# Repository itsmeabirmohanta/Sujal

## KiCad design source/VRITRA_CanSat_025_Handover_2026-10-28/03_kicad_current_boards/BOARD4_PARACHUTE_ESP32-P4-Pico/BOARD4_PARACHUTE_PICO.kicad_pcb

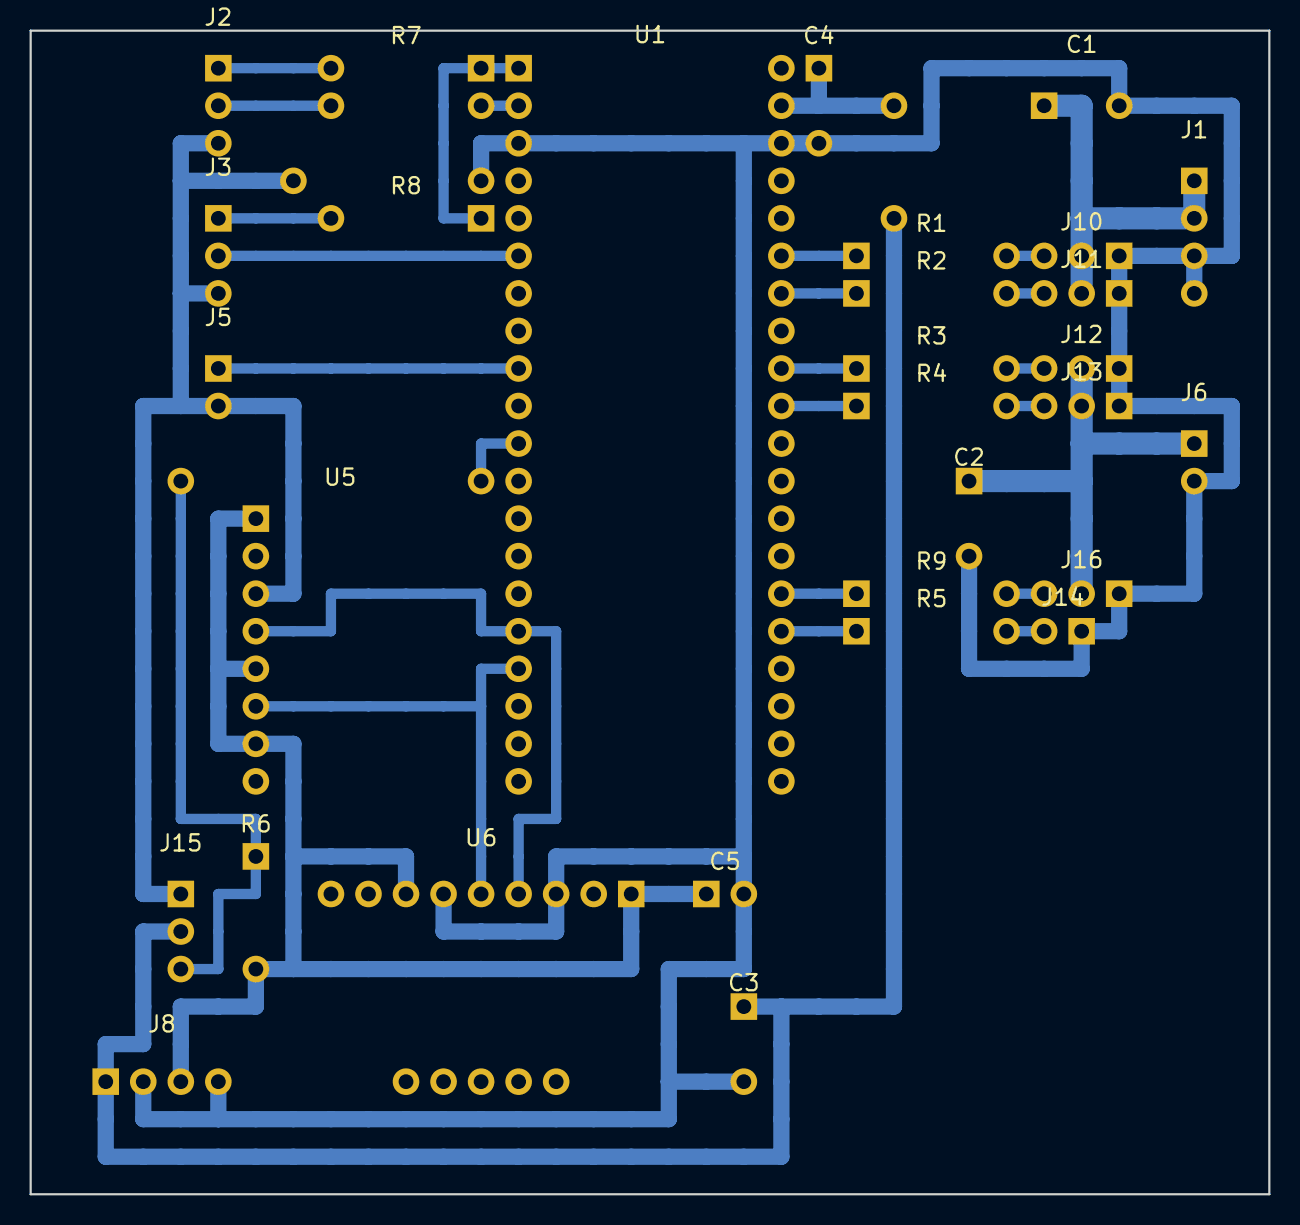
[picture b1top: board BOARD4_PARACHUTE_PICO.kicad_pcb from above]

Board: 2 copper layers, 83.8 x 78.7 mm, 34 parts (0 on the bottom side), 26 nets.

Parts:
C1: 470µF 8V rail
C2: 470µF 5VS rail
C3: 470µF logic
C4: 100nF at VSYS
C5: 100nF
J1: 8 V steer in (POWER J8)
J2: UART from MAIN J4
J3: UART to BACKUP J3
J5: GNSS from MAIN J8
J6: 5 V servo in (POWER J9)
J8: logic PWR (POWER J7)
J10: A20CLM LEFT steer (8 V)
J11: A20CLM RIGHT steer (8 V)
J12: MG90S #1 PARACHUTE BAY
J13: MG90S #2 PETRI PLATE
J14: ESC signal
J15: HALL sensor plug
J16: MG90S #3 EXTRA
LK1, LK2, LK3, LK4: wire link
R1, R2, R3, R4, R5, R9: 330
R6: 10k HALL↑3V3
R7: 1k TX2→A
R8: 1k TX→B
U1: ESP32-P4-Pico
U5: BMP585 (7Semi)
U6: LSM6DSO32 (Adafruit)

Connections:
+3V3_B: C5.1, J8.3 (+3V3), R6.2, U5.1 (VIN), U5.5 (SDO), U5.7 (CS), U6.1 (VIN), U6.7 (CS)
+5V_LOGIC: C3.1 (+), C4.1, J8.1 (+5V), J15.2 (+5V), LK1.1, U1.39 (VSYS)
+5V_SERVO: C2.1 (+), J6.1 (+5VS), J12.2 (+), J13.2 (+), J16.2 (+)
+8V_STEER: C1.1 (+), J1.1 (+8V), J1.2 (+8V), J10.2 (+), J11.2 (+)
BAY_LID: R3.1, U1.32 (GPIO22)
BAY_LID_S: J12.3 (S), R3.2
ESC: R5.1, U1.25 (GPIO33)
ESC_S: J14.2 (S), R5.2
GND: C1.2 (-), C2.2 (-), C3.2 (-), C4.2, C5.2, J1.3 (GND), J1.4 (GND), J2.3 (GND), J3.3 (GND), J5.2 (GND), J6.2 (GND), J8.2 (GND), J8.4 (GND), J10.1 (−), J11.1 (−), J12.1 (−), J13.1 (−), J14.1 (−), J15.1 (−), J16.1 (−), LK3.1, U1.3 (GND), U1.38 (GND), U5.3 (GND), U6.3 (GND), U6.6 (DO)
GNSS_IN: J5.1 (GNSS), U1.9 (GPIO14)
HALL: J15.3 (OUT), LK2.1, R6.1, U1.11 (GPIO5)
PETRI: R4.1, U1.31 (GPIO23)
PETRI_S: J13.3 (S), R4.2
RX2: J2.2 (RX2←A), LK4.1, U1.2 (GPIO19)
RX3: J3.2 (RX3←B), U1.6 (GPIO16)
SCL: U1.16 (GPIO8/SCL), U5.4 (SCK), U6.4 (SCL)
SDA: U1.17 (GPIO7/SDA), U5.6 (SDI), U6.5 (SDA)
SERVO_X: R9.1, U1.26 (GPIO32)
SERVO_X_S: J16.3 (S), R9.2
STEER_L: R1.1, U1.35 (GPIO20)
STEER_L_S: J10.3 (S), R1.2
STEER_R: R2.1, U1.34 (GPIO21)
STEER_R_S: J11.3 (S), R2.2
TX2: R7.1, R8.1, U1.1 (GPIO54)
TX2_A: J2.1 (TX2→A), R7.2
TX2_B: J3.1 (TX→B), R8.2

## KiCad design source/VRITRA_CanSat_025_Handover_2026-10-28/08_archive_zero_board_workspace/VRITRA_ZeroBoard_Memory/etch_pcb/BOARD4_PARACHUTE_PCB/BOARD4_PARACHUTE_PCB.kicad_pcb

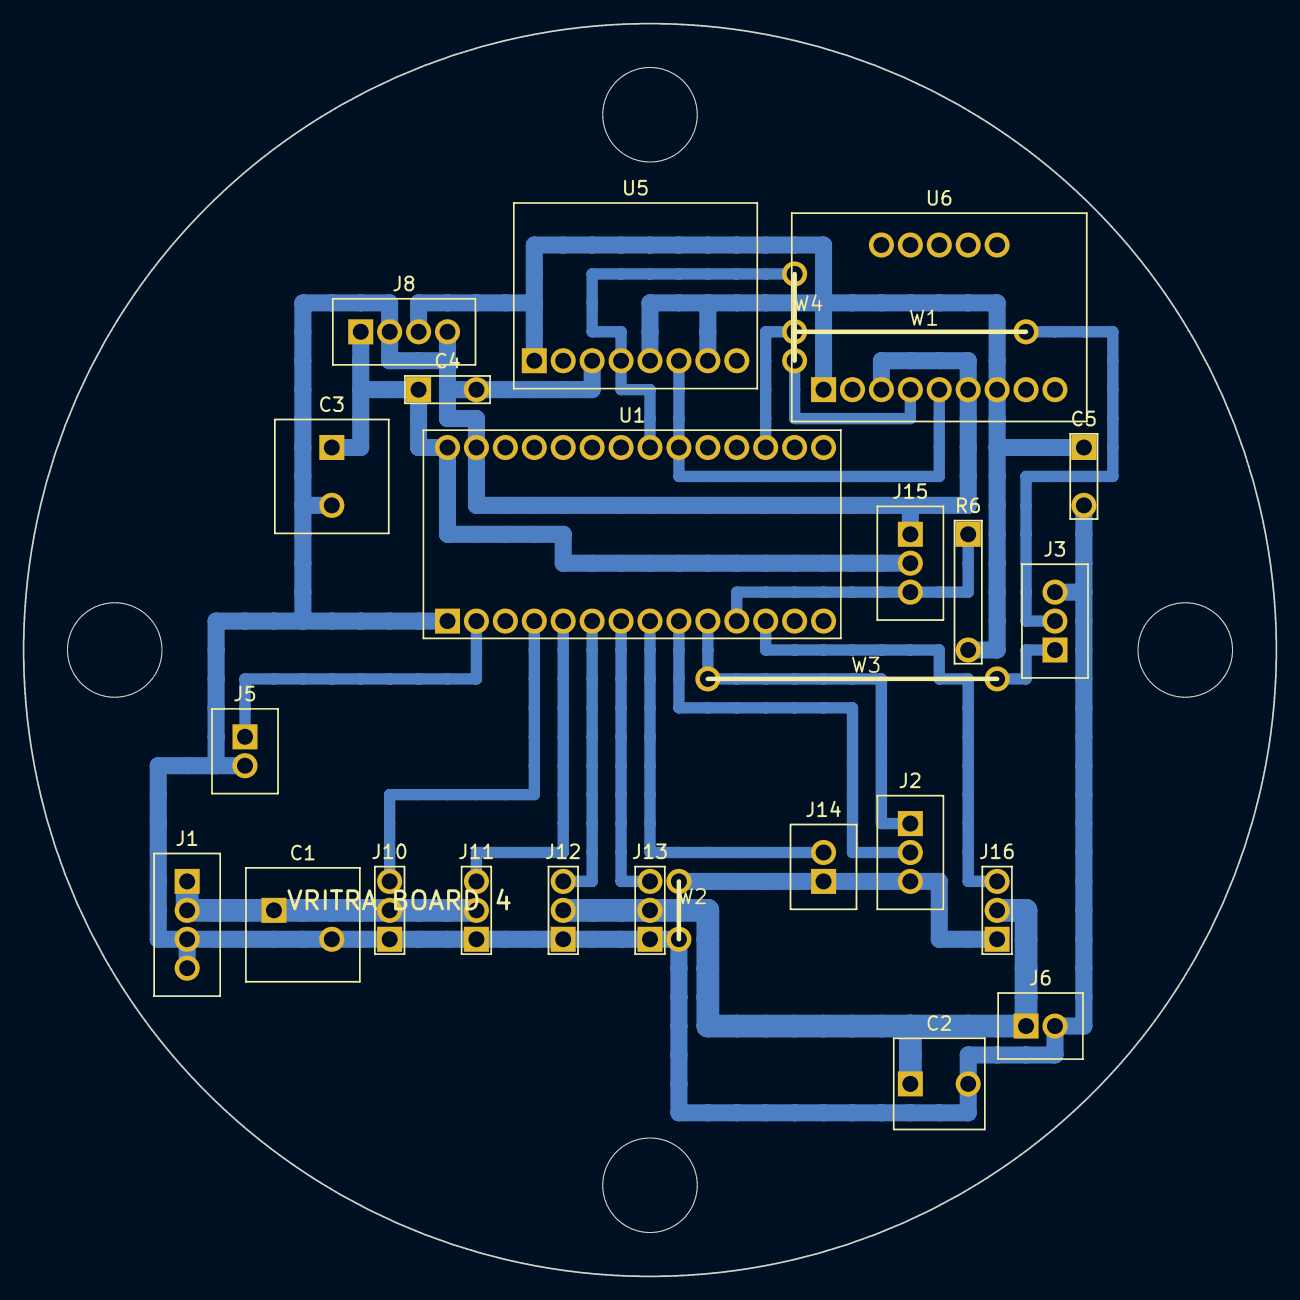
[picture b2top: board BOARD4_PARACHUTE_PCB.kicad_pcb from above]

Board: 2 copper layers, 110.0 x 110.0 mm, 30 parts (0 on the bottom side), 18 nets.

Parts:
C1: 470µF 8V rail
C2: 470µF 5VS rail
C3: 470µF logic
C4, C5: 100nF
J1: 8 V steer in (POWER J8)
J2: UART from MAIN J4
J3: UART to BACKUP J3
J5: GNSS from MAIN J8
J6: 5 V servo in (POWER J9)
J8: logic PWR (POWER J7)
J10: A20CLM LEFT steer (8 V)
J11: A20CLM RIGHT steer (8 V)
J12: MG90S #1 PARACHUTE BAY
J13: MG90S #2 PETRI PLATE
J14: ESC signal (Cyclone 45A BLHeli_S)
J15: HALL sensor plug (sensor on the body)
J16: MG90S #3 EXTRA
R6: 10k HALL↑3V3
ROD1, ROD2, ROD3, ROD4: rod Ø8.3
U1: Teensy 4.0 PARACHUTE
U5: BMP585 #3
U6: LSM6DSO32 (Adafruit)
W1, W2, W3, W4: wire jumper

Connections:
+3V3_B: C5.1, J8.3, R6.2, U5.1, U5.5, U5.7, U6.1, U6.7
+5V_LOGIC: C3.1, C4.1, J8.1, J15.2, U1.28
+5V_SERVO: C2.1, J6.1, J12.2, J13.2, J16.2
+8V_STEER: C1.1, J1.1, J1.2, J10.2, J11.2
BAY_LID: J12.3, U1.6
ESC: J14.2, U1.8
GND: C1.2, C2.2, C3.2, C4.2, C5.2, J1.3, J1.4, J2.3, J3.3, J5.2, J6.2, J8.2, J8.4, J10.1, J11.1, J12.1, J13.1, J14.1, J15.1, J16.1, U1.1, U1.27, U5.3, U6.3, U6.6, W2.1
GNSS_IN: J5.1, U1.2
HALL: J15.3, R6.1, U1.11
PETRI: J13.3, U1.7
RX2: J2.2, U1.9
RX3: J3.2, U1.17, W1.1
SCL: U1.21, U5.4, U6.4, W4.1
SDA: U1.20, U5.6, U6.5
SERVO_X: J16.3, U1.12
STEER_L: J10.3, U1.4
STEER_R: J11.3, U1.5
TX2: J2.1, J3.1, U1.10, W3.1

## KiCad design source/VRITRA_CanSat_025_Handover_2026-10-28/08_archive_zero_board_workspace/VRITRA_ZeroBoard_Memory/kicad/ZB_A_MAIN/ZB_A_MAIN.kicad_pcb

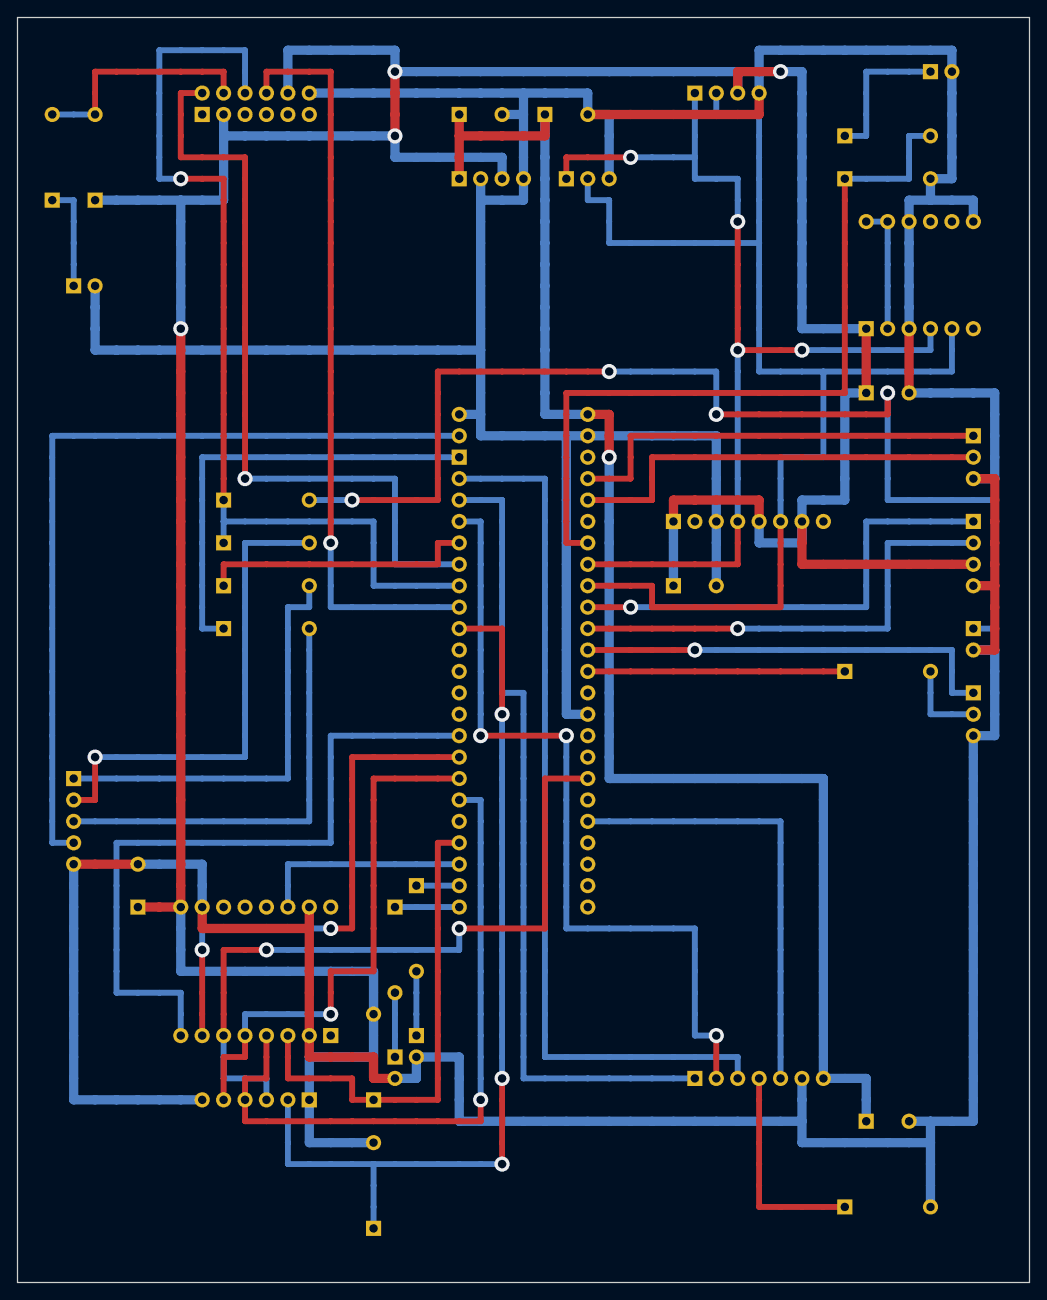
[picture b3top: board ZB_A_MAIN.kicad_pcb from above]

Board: 2 copper layers, 120.0 x 150.0 mm, 39 parts (0 on the bottom side), 44 nets.

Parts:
C1: 470µF
C2, C3, C4, C5: 100nF
C6: 100µF amp
D1: LED green
D2: LED red
D3: Schottky 3V3→BAT
D4: Schottky cell→BAT
J1: PWR from E J5
J2: I2C to E J2
J3: VBAT from E J10
J4: UART to D J2
J5: LINK cable to BACKUP J2
J6: I2C to C J1
J7: GNSS backup cell
J8: GNSS to D J5
J9: analog to C J7
R1: 10k LORA_CS↑
R2: 10k FLASH_CS↑
R3: 1k HB
R4: 1k TX3
R5: 1k GNSS→D
R6: 1k GNSS→B
R7: 100k VBAT
R8: 22k VBAT
R9: 470 LED OK
R10: 470 LED FLT
R11: 1k CAM TX
R12: 100k GAIN↓ 15dB
U1: Teensy 4.1 PRIMARY
U2: Core1121-HF
U3: L89HA GNSS
U4: DS3231 (MH ZS-042)
U5: BMP585 #1
U6: ICM-20948 #1
U7: W25Q64 flash
U9: MAX98357A beacon amp

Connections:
+3V3_A: C3.1, C4.1, C5.1, D3.1 (A), J1.3 (+3V3), J6.3 (3V3), R1.2, R2.2, U2.16 (3.3V), U3.2 (WAKE), U3.11 (3V3), U4.3 (VCC), U5.1 (VIN), U5.5 (SDO), U5.7 (CS), U6.1 (VIN), U7.1 (3V3)
+5V_LOGIC: C1.1 (+), C2.1, C6.1 (+), J1.1 (+5V), U1.VIN, U9.7 (Vin)
AMP_BCLK: U1.4, U9.2 (BCLK)
AMP_DIN: U1.2, U9.3 (DIN)
AMP_GAIN: R12.1, U9.4 (GAIN)
AMP_LRC: U1.3, U9.1 (LRC)
AMP_SD: U1.37, U9.5 (SD)
BUS_V: R7.2, R8.1, U1.20
CAM_RX: J5.4 (MUX_RX), U1.0
CAM_TX: R11.1, U1.1
CAM_TX_J: J5.3 (MUX_TX), R11.2
ENV_O3: J9.1 (O3), U1.23
ENV_UV: J9.2 (UV), U1.22
FLASH_CS: R2.1, U1.9, U7.2 (CS)
GND: C1.2 (-), C2.2, C3.2, C4.2, C5.2, C6.2 (-), D1.2 (K), D2.2 (K), J1.2 (GND), J1.4 (GND), J2.3 (GND), J3.2 (GND), J4.3 (GND), J5.5 (GND), J6.4 (GND), J7.2 (GND), J8.2 (GND), J9.3 (GND), R8.2, R12.2, U1.GND1 (GND), U1.GND2 (GND), U1.GND3 (GND), U2.2 (GND), U2.10 (GND), U2.15 (GND), U3.12 (GND), U4.4 (GND), U5.3 (GND), U6.3 (GND), U6.9 (GND), U6.12 (FSYNC), U7.6 (GND), U9.6 (GND)
GNSS_B: J5.2 (GNSS), R6.2
GNSS_CELL: D4.1 (A), J7.1 (CELL+)
GNSS_D: J8.1 (GNSS), R5.2
GNSS_RST: U1.6, U3.7 (RST)
GNSS_RX: U1.8, U3.10 (RX)
GNSS_TX: R5.1, R6.1, U1.7, U3.9 (TX)
GNSS_VBCKP: D3.2 (K), D4.2 (K), U3.8 (BAT)
HB_J5: J5.1 (HB), R3.2
HB_OUT: R3.1, U1.5
ICM_1V8: U6.2 (1V8), U6.7 (CS), U6.8 (SDO)
LED_FLT: R10.1, U1.32
LED_FLT_A: D2.1 (A), R10.2
LED_OK: R9.1, U1.31
LED_OK_A: D1.1 (A), R9.2
LORA_BUSY: U1.24, U2.8 (BUSY)
LORA_CS: R1.1, U1.29, U2.3 (CS)
LORA_IRQ: U1.30, U2.11 (DIO9)
LORA_RST: U1.25, U2.7 (RESET)
MISO1: U1.39, U2.6 (MISO), U7.3 (MISO)
MOSI1: U1.26, U2.5 (MOSI), U7.5 (MOSI)
RX3: J4.1 (RX3), U1.15
SCK1: U1.27, U2.4 (CLK), U7.4 (SCK)
SCL: J2.1 (SCL), U1.19, U4.1 (SCL), U5.4 (SCK), U6.4 (SCL)
SCL1: J6.2 (SCL1), U1.16
SDA: J2.2 (SDA), U1.18, U4.2 (SDA), U5.6 (SDI), U6.5 (SDA)
SDA1: J6.1 (SDA1), U1.17
TX3: R4.1, U1.14
TX3_J4: J4.2 (TX3), R4.2
VBAT_SENSE: J3.1 (VBAT), R7.1

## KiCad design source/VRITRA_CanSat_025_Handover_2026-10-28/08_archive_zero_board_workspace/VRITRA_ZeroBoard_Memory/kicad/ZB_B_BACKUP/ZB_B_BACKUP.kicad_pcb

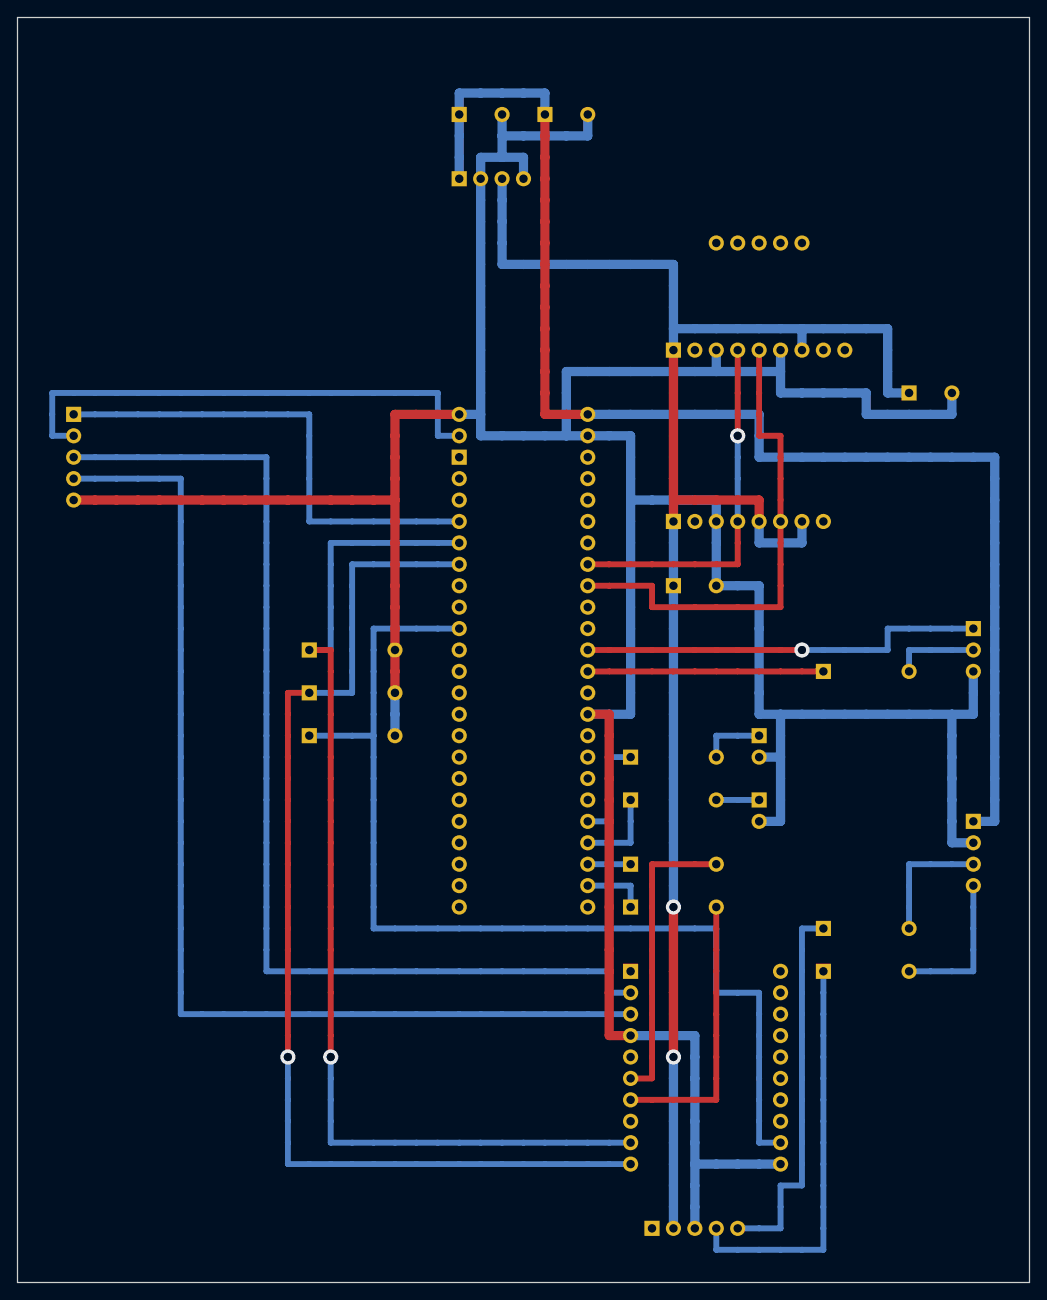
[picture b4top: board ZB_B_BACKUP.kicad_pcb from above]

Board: 2 copper layers, 120.0 x 150.0 mm, 25 parts (0 on the bottom side), 27 nets.

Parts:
C1: 470µF
C2, C3, C4: 100nF
D1: LED green
D2: LED red
J1: PWR from E J6
J2: LINK cable from MAIN J5
J3: to D J3
J4: CAMERA plug (the only one)
R1: 1k TX3
R2: 1k TX8
R3: 1k RX8
R4: 470 LED OK
R5: 470 LED FLT
R6: 10k MUX_A↓
R7: 10k MUX_B↓
R8: 10k MUX_C↓
R9: 1k cam RX
R10: 1k cam TX
U1: Teensy 4.1 BACKUP
U5: BMP585 #2
U8: LSM6DSO32 (Adafruit)
U10: 7Semi UART mux
U10B: mux bottom-row wires

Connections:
+3V3_B: C3.1, C4.1, J1.3 (+3V3), U5.1 (VIN), U5.5 (SDO), U5.7 (CS), U8.1 (VIN), U8.7 (CS), U10B.2 (3V3)
+5V_LOGIC: C1.1 (+), C2.1, J1.1 (+5V), J4.1 (+5V), U1.VIN
CAM_COM_RX: R10.1, U10B.4 (RX_COM)
CAM_COM_TX: R9.1, U10B.5 (TX_COM)
CAM_FROM_XIAO: J4.4 (from D6), R10.2
CAM_RX: J2.4 (MUX_RX), U10.3 (RX1)
CAM_TO_XIAO: J4.3 (to D7), R9.2
CAM_TX_J: J2.3 (MUX_TX), U10.2 (TX1)
GND: C1.2 (-), C2.2, C3.2, C4.2, D1.2 (K), D2.2 (K), J1.2 (GND), J1.4 (GND), J2.5 (GND), J3.3 (GND), J4.2 (GND), R6.2, R7.2, R8.2, U1.GND1 (GND), U1.GND2 (GND), U1.GND3 (GND), U5.3 (GND), U8.3 (GND), U8.6 (DO), U10.4 (GND), U10.20 (GND), U10B.3 (GND)
GNSS_IN: J2.2 (GNSS), U1.0
HB_IN: J2.1 (HB), U1.4
LED_FLT: R5.1, U1.37
LED_FLT_A: D2.1 (A), R5.2
LED_OK: R4.1, U1.36
LED_OK_A: D1.1 (A), R4.2
MUX_A: R6.1, U1.5, U10.9 (A)
MUX_B: R7.1, U1.6, U10.10 (B)
MUX_C: R8.1, U1.9, U10.19 (C)
RX3: J3.1 (RX3), U1.15
RX8: R3.1, U1.34
RX8_J: R3.2, U10.7 (RX2)
SCL: U1.19, U5.4 (SCK), U8.4 (SCL)
SDA: U1.18, U5.6 (SDI), U8.5 (SDA)
TX3: R1.1, U1.14
TX3_J: J3.2 (TX3), R1.2
TX8: R2.1, U1.35
TX8_J: R2.2, U10.6 (TX2)

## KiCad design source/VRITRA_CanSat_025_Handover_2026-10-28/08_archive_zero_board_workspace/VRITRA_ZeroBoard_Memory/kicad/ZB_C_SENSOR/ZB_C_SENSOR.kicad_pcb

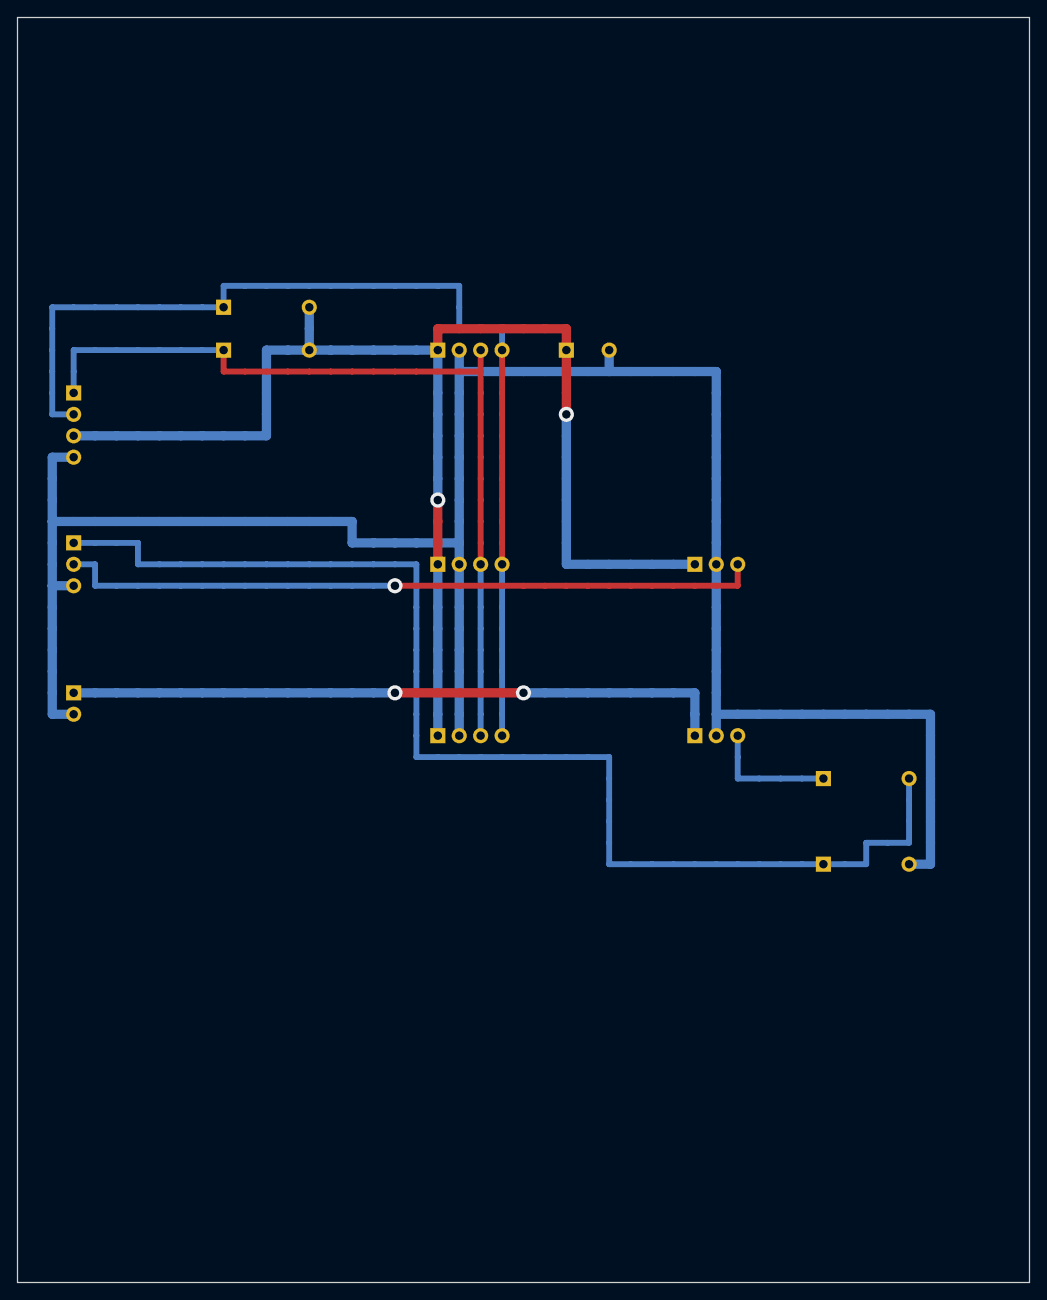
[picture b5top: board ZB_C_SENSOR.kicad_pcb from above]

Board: 2 copper layers, 120.0 x 150.0 mm, 13 parts (0 on the bottom side), 8 nets.

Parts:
C1: 100nF
J1: I2C from A J6
J2: HDC3020 cable
J3: 5V from E J11
J4: I²C sensor #1
J5: ML8511 UV
J6: MQ-131
J7: analog from A J9
J8: I²C sensor #2
R1: 4.7k SDA1↑ (fit if needed)
R2: 4.7k SCL1↑ (fit if needed)
R4: 10k MQ divider top
R5: 20k (2×10k) bottom

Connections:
+3V3_A: C1.1, J1.3 (3V3), J2.1 (3V3), J4.1 (3V3), J5.1 (3V3), J8.1 (3V3), R1.2, R2.2
+5V_MQ: J3.1 (+5V), J6.1 (+5V)
ENV_O3: J7.1 (O3), R4.2, R5.1
ENV_UV: J5.3 (UV), J7.2 (UV)
GND: C1.2, J1.4 (GND), J2.2 (GND), J3.2 (GND), J4.2 (GND), J5.2 (GND), J6.2 (GND), J7.3 (GND), J8.2 (GND), R5.2
MQ_AO: J6.3 (AO), R4.1
SCL1: J1.2 (SCL1), J2.4 (SCL), J4.4 (SCL), J8.4 (SCL), R2.1
SDA1: J1.1 (SDA1), J2.3 (SDA), J4.3 (SDA), J8.3 (SDA), R1.1

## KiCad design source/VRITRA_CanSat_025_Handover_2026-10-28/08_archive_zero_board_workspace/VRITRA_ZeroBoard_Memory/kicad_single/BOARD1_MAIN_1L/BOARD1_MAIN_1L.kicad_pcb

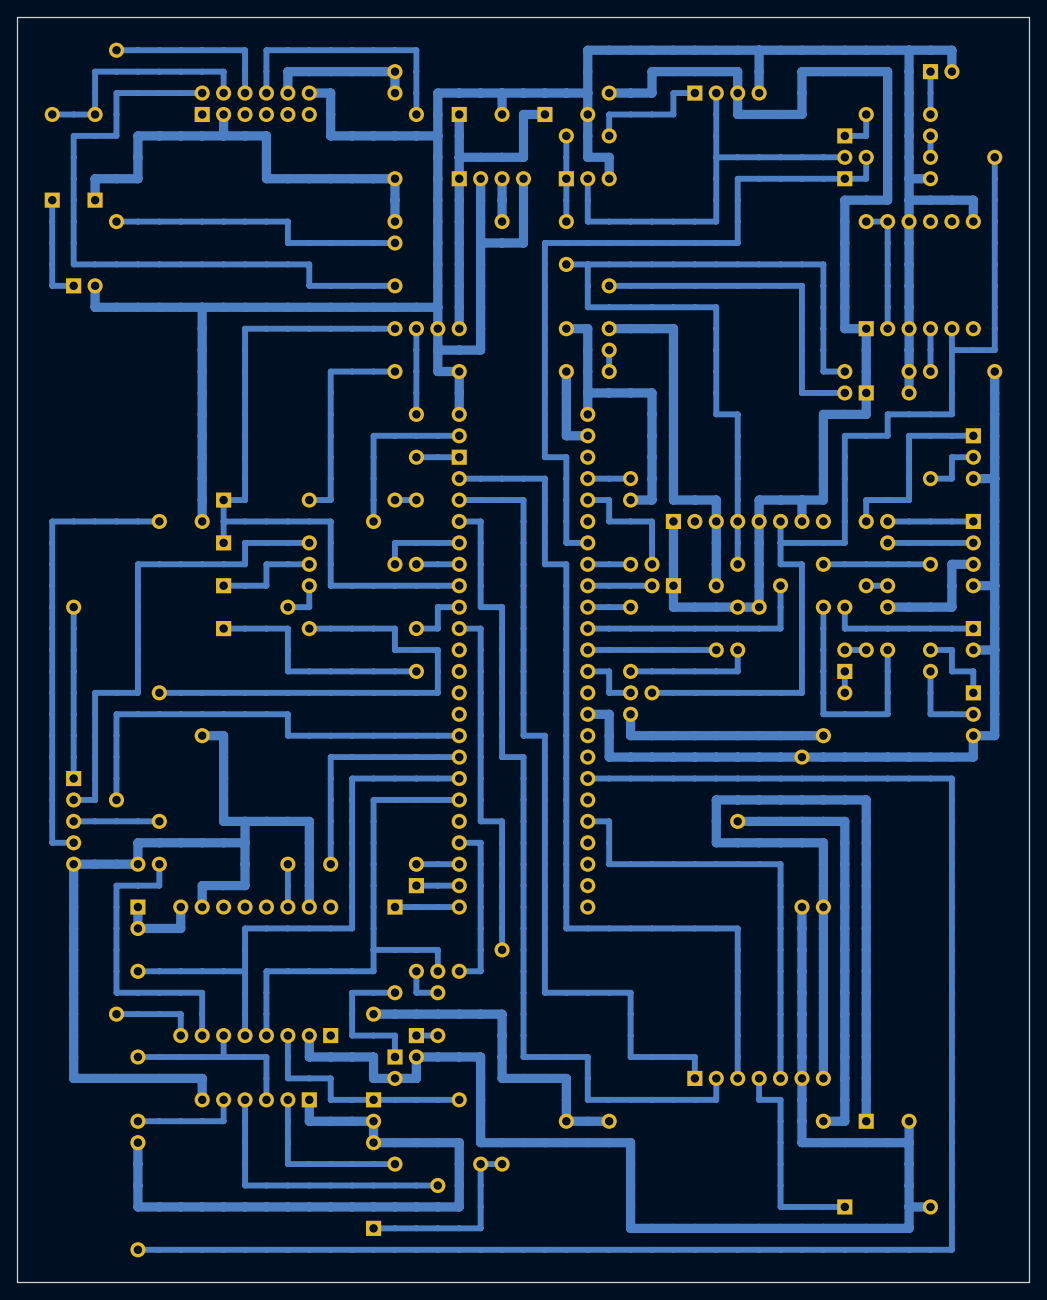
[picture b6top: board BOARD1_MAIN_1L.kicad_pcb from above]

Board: 2 copper layers, 120.0 x 150.0 mm, 98 parts (0 on the bottom side), 44 nets.

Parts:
C1: 470µF
C2, C3, C4, C5: 100nF
C6: 100µF amp
D1: LED green
D2: LED red
D3: Schottky 3V3→BAT
D4: Schottky cell→BAT
J1: PWR from E J5
J2: I2C to E J2
J3: VBAT from E J10
J4: UART to D J2
J5: LINK cable to BACKUP J2
J6: I2C to C J1
J7: GNSS backup cell
J8: GNSS to D J5
J9: analog to C J7
LK1, LK2, LK3, LK4, LK5, LK6, LK7, LK8, LK9, LK10, LK11, LK12, LK13, LK14, LK15, LK16, LK17, LK18, LK19, LK20, LK21, LK22, LK23, LK24, LK25, LK26, LK27, LK28, LK29, LK30, LK31, LK32, LK33, LK34, LK35, LK36, LK37, LK38, LK39, LK40, LK41, LK42, LK43, LK44, LK45, LK46, LK47, LK48, LK49, LK50, LK51, LK52, LK53, LK54, LK55, LK56, LK57, LK58, LK59: wire link
R1: 10k LORA_CS↑
R2: 10k FLASH_CS↑
R3: 1k HB
R4: 1k TX3
R5: 1k GNSS→D
R6: 1k GNSS→B
R7: 100k VBAT
R8: 22k VBAT
R9: 470 LED OK
R10: 470 LED FLT
R11: 1k CAM TX
R12: 100k GAIN↓ 15dB
U1: Teensy 4.1 PRIMARY
U2: Core1121-HF
U3: L89HA GNSS
U4: DS3231 (MH ZS-042)
U5: BMP585 #1
U6: ICM-20948 #1
U7: W25Q64 flash
U9: MAX98357A beacon amp

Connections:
+3V3_A: C3.1, C4.1, C5.1, D3.1 (A), J1.3 (+3V3), J6.3 (3V3), LK47.1, LK48.1, LK49.1, LK50.1, LK51.1, LK52.1, LK53.1, LK54.1, R1.2, R2.2, U2.16 (3.3V), U3.2 (WAKE), U3.11 (3V3), U4.3 (VCC), U5.1 (VIN), U5.5 (SDO), U5.7 (CS), U6.1 (VIN), U7.1 (3V3)
+5V_LOGIC: C1.1 (+), C2.1, C6.1 (+), J1.1 (+5V), LK44.1, LK45.1, LK46.1, U1.VIN, U9.7 (Vin)
AMP_BCLK: U1.4, U9.2 (BCLK)
AMP_DIN: U1.2, U9.3 (DIN)
AMP_GAIN: R12.1, U9.4 (GAIN)
AMP_LRC: U1.3, U9.1 (LRC)
AMP_SD: U1.37, U9.5 (SD)
BUS_V: LK31.1, R7.2, R8.1, U1.20
CAM_RX: J5.4 (MUX_RX), LK34.1, U1.0
CAM_TX: LK6.1, R11.1, U1.1
CAM_TX_J: J5.3 (MUX_TX), LK9.1, R11.2
ENV_O3: J9.1 (O3), LK13.1, LK14.1, LK15.1, U1.23
ENV_UV: J9.2 (UV), LK11.1, LK12.1, U1.22
FLASH_CS: LK32.1, LK33.1, R2.1, U1.9, U7.2 (CS)
GND: C1.2 (-), C2.2, C3.2, C4.2, C5.2, C6.2 (-), D1.2 (K), D2.2 (K), J1.2 (GND), J1.4 (GND), J2.3 (GND), J3.2 (GND), J4.3 (GND), J5.5 (GND), J6.4 (GND), J7.2 (GND), J8.2 (GND), J9.3 (GND), LK55.1, LK56.1, LK57.1, LK58.1, LK59.1, R8.2, R12.2, U1.GND1 (GND), U1.GND2 (GND), U1.GND3 (GND), U2.2 (GND), U2.10 (GND), U2.15 (GND), U3.12 (GND), U4.4 (GND), U5.3 (GND), U6.3 (GND), U6.9 (GND), U6.12 (FSYNC), U7.6 (GND), U9.6 (GND)
GNSS_B: J5.2 (GNSS), R6.2
GNSS_CELL: D4.1 (A), J7.1 (CELL+)
GNSS_D: J8.1 (GNSS), LK35.1, LK36.1, LK37.1, R5.2
GNSS_RST: LK29.1, LK30.1, U1.6, U3.7 (RST)
GNSS_RX: LK25.1, LK26.1, U1.8, U3.10 (RX)
GNSS_TX: LK27.1, LK28.1, R5.1, R6.1, U1.7, U3.9 (TX)
GNSS_VBCKP: D3.2 (K), D4.2 (K), U3.8 (BAT)
HB_J5: J5.1 (HB), LK8.1, R3.2
HB_OUT: LK5.1, R3.1, U1.5
ICM_1V8: U6.2 (1V8), U6.7 (CS), U6.8 (SDO)
LED_FLT: R10.1, U1.32
LED_FLT_A: D2.1 (A), R10.2
LED_OK: R9.1, U1.31
LED_OK_A: D1.1 (A), LK1.1, R9.2
LORA_BUSY: LK23.1, U1.24, U2.8 (BUSY)
LORA_CS: LK7.1, R1.1, U1.29, U2.3 (CS)
LORA_IRQ: LK3.1, U1.30, U2.11 (DIO9)
LORA_RST: LK21.1, U1.25, U2.7 (RESET)
MISO1: LK24.1, U1.39, U2.6 (MISO), U7.3 (MISO)
MOSI1: LK22.1, U1.26, U2.5 (MOSI), U7.5 (MOSI)
RX3: J4.1 (RX3), LK10.1, U1.15
SCK1: LK20.1, U1.27, U2.4 (CLK), U7.4 (SCK)
SCL: J2.1 (SCL), LK38.1, LK39.1, LK40.1, LK41.1, U1.19, U4.1 (SCL), U5.4 (SCK), U6.4 (SCL)
SCL1: J6.2 (SCL1), LK18.1, LK19.1, U1.16
SDA: J2.2 (SDA), LK42.1, LK43.1, U1.18, U4.2 (SDA), U5.6 (SDI), U6.5 (SDA)
SDA1: J6.1 (SDA1), LK16.1, LK17.1, U1.17
TX3: LK4.1, R4.1, U1.14
TX3_J4: J4.2 (TX3), R4.2
VBAT_SENSE: J3.1 (VBAT), LK2.1, R7.1

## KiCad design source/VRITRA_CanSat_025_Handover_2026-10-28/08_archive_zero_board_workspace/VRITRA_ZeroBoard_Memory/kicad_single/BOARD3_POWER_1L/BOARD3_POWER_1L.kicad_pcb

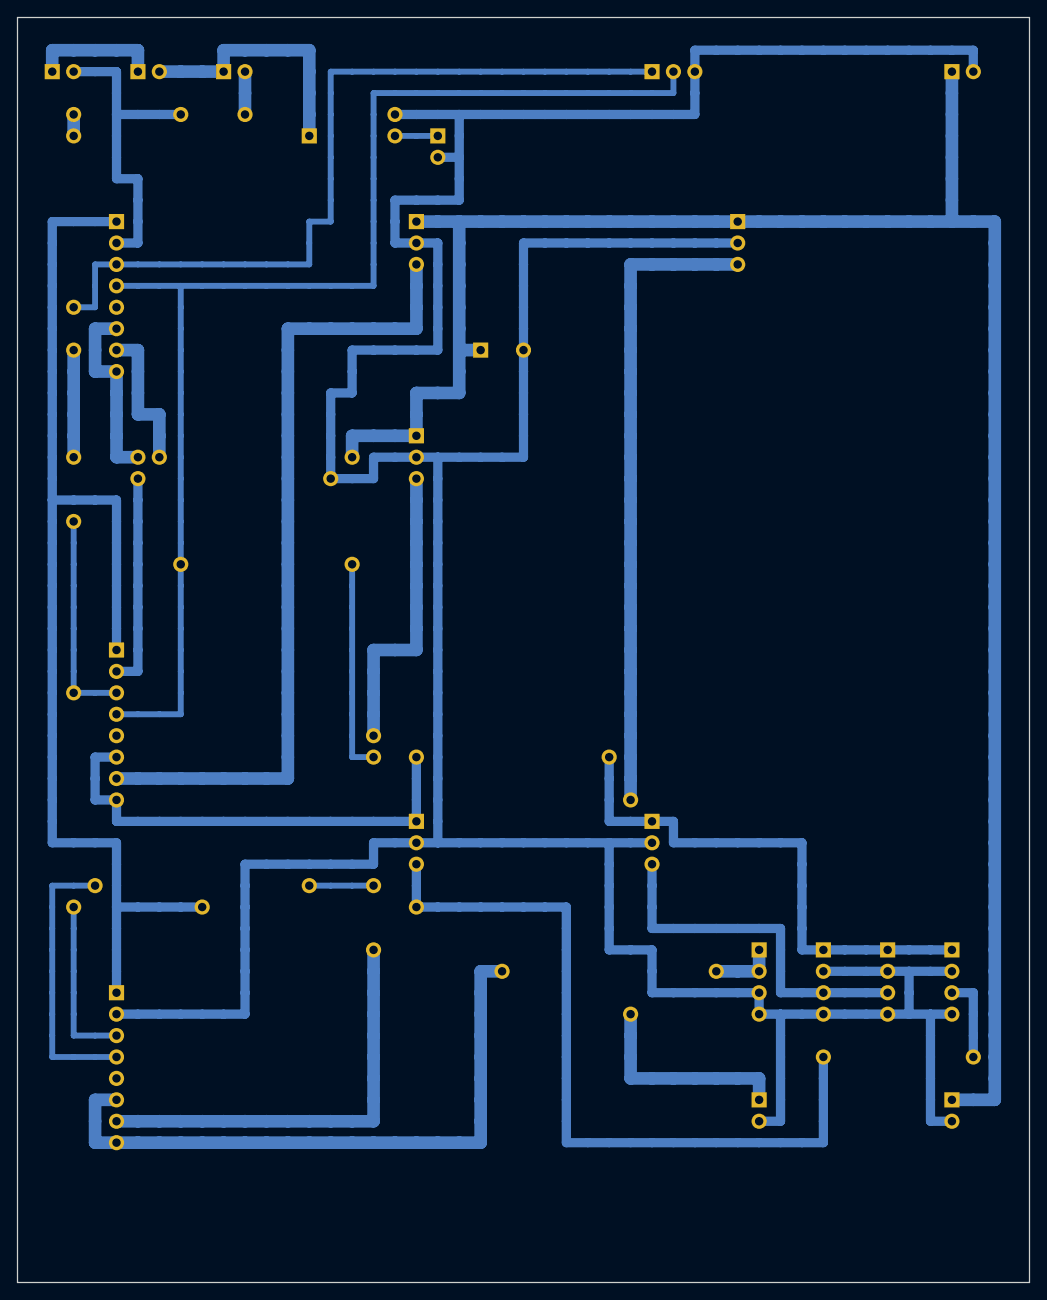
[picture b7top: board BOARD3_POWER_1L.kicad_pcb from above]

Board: 2 copper layers, 120.0 x 150.0 mm, 39 parts (0 on the bottom side), 15 nets.

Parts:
C1: 470µF 25V VBAT
D1: PWR LED red
F1: FUSE 10 A (link until fitted)
J1: BATTERY (XT60 lead)
J2: I²C to A J2
J3: rocker switch (shell)
J4: ESC (XT30 lead)
J5: PWR to A J1
J6: PWR to B J1
J7: PWR to D J8
J8: 8 V → PARACHUTE J1
J9: 5 V servo → PARACHUTE J6
J10: VBAT sense to A J3
LK1, LK2, LK3, LK4, LK5, LK6, LK7, LK8, LK9, LK10, LK11, LK12, LK13, LK14, LK15, LK16, LK17: wire link
M1L: M1 landing
M2L: M2 landing
M3L: M3 landing
M4L: M4 landing
M5L: M5 landing
R1: 1k LED
U1: INA260 #1 BATTERY
U2: INA260 #2 8V STEER
U3: INA260 #3 5V LOGIC

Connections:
5V_RAW: M1L.3 (OUT), U3.7 (IN+)
8V_RAW: LK6.1, M3L.3 (OUT), U2.7 (IN+)
+3V3_A: J5.3 (+3V3_A), LK13.1, LK14.1, M4L.3 (OUT), U1.1 (VCC), U2.1 (VCC), U3.1 (VCC)
+3V3_B: J6.3 (+3V3_B), J7.3 (+3V3_B), M5L.3 (OUT)
+5V_LOGIC: J5.1 (+5V), J6.1 (+5V), J7.1 (+5V), LK7.1, M4L.1 (IN), M5L.1 (IN), U3.6 (VBUS), U3.8 (IN-)
+5V_SERVO: J9.1 (+5VS), LK5.1, M2L.3 (OUT)
+8V_STEER: J8.1 (+8V), J8.2 (+8V), LK4.1, U2.6 (VBUS), U2.8 (IN-)
BAT+: J1.1 (BAT+), J3.1 (SW_A)
GND: C1.2 (-), D1.2 (K), J1.2 (BAT−), J2.3 (GND), J4.2 (GND), J5.2 (GND), J5.4 (GND), J6.2 (GND), J6.4 (GND), J7.2 (GND), J7.4 (GND), J8.3 (GND), J8.4 (GND), J9.2 (GND), J10.2 (GND), LK16.1, LK17.1, M1L.2 (GND), M2L.2 (GND), M3L.2 (GND), M4L.2 (GND), M5L.2 (GND), U1.2 (GND), U2.2 (GND), U3.2 (GND)
LED_A: D1.1 (A), R1.2
SCL: J2.1 (SCL), LK8.1, LK9.1, U1.3 (SCL), U2.3 (SCL), U3.3 (SCL)
SDA: J2.2 (SDA), LK10.1, LK11.1, LK12.1, U1.4 (SDA), U2.4 (SDA), U3.4 (SDA)
VBAT: C1.1 (+), J4.1 (VBAT), J10.1 (VBAT), LK15.1, M1L.1 (IN), M2L.1 (IN), M3L.1 (IN), U1.6 (VBUS), U1.8 (IN-)
VBAT_F: F1.2 (OUT), LK1.1, LK2.1, LK3.1, U1.7 (IN+)
VBAT_SW: F1.1 (IN), J3.2 (SW_B), R1.1
